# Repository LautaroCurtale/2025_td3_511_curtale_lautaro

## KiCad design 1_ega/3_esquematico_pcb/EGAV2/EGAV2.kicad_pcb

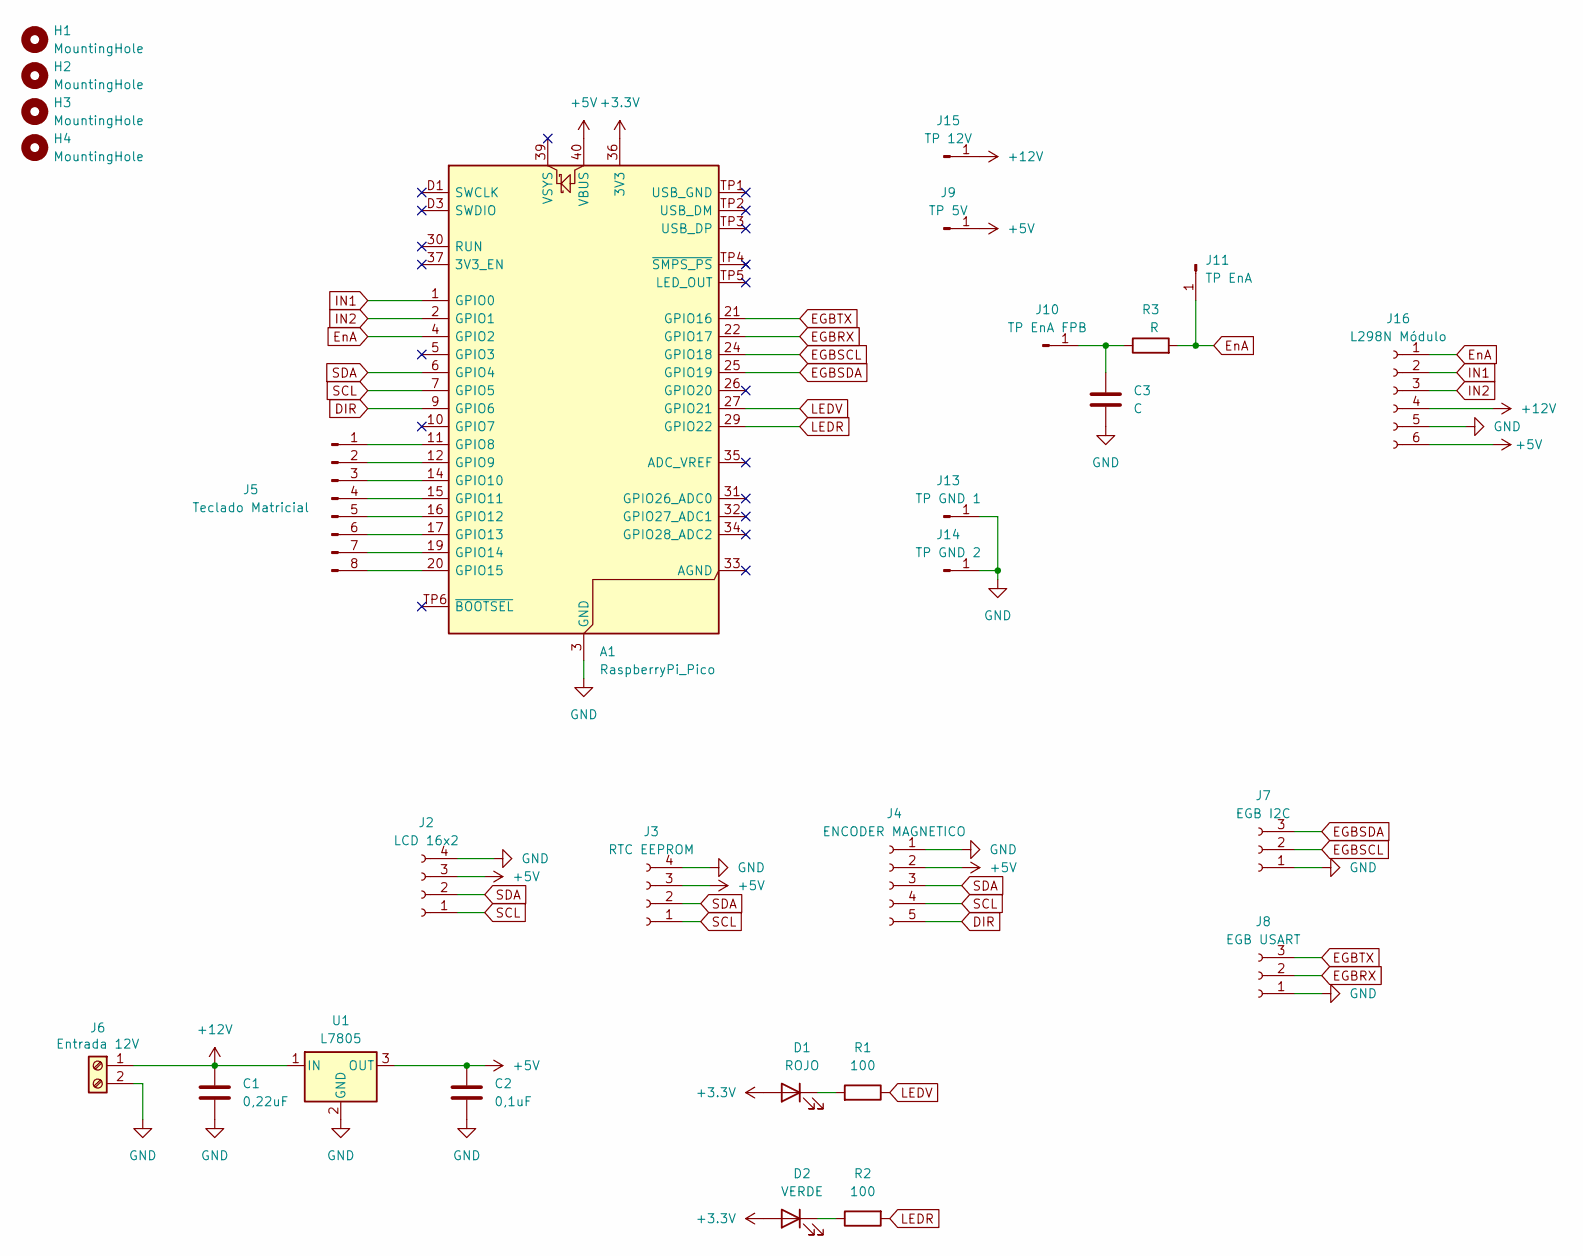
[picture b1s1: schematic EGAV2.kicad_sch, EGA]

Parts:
A1: RaspberryPi_Pico; RaspberryPi_Pico_Common_THT
C1: 0,22uF; C_Disc_D3.0mm_W2.0mm_P2.50mm
C2: 0,1uF; C_Disc_D3.0mm_W2.0mm_P2.50mm
C3: C; C_Disc_D3.0mm_W2.0mm_P2.50mm
D1: ROJO; LED_D5.0mm
D2: VERDE; LED_D5.0mm
H1, H2, H3, H4: MountingHole; MountingHole_3mm
J2: LCD 16x2; PinSocket_1x04_P2.54mm_Vertical
J3: RTC EEPROM; PinSocket_1x04_P2.54mm_Vertical
J4: ENCODER MAGNETICO; PinHeader_1x05_P2.54mm_Vertical
J5: Teclado Matricial; PinHeader_1x08_P2.54mm_Vertical
J6: Entrada 12V; TerminalBlock_Phoenix_MKDS-1,5-2-5.08_1x02_P5.08mm_Horizont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
J7: EGB I2C; PinHeader_1x03_P2.54mm_Vertical
J8: EGB USART; PinHeader_1x03_P2.54mm_Vertical
J9: TP 5V; PinHeader_1x01_P2.54mm_Vertical
J10: TP EnA FPB; PinHeader_1x01_P2.54mm_Vertical
J11: TP EnA; PinHeader_1x01_P2.54mm_Vertical
J13: TP GND 1; PinHeader_1x01_P2.54mm_Vertical
J14: TP GND 2; PinHeader_1x01_P2.54mm_Vertical
J15: TP 12V; PinHeader_1x01_P2.54mm_Vertical
J16: L298N Módulo; PinHeader_1x06_P2.54mm_Vertical
R1, R2: 100; R_Axial_DIN0207_L6.3mm_D2.5mm_P10.16mm_Horizontal
R3: R; R_Axial_DIN0207_L6.3mm_D2.5mm_P10.16mm_Horizontal
U1: L7805; TO-220-3_Vertical

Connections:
+3.3V: A1.36 (3V3), D1.2 (A), D2.2 (A)
+5V: A1.40 (VBUS), C2.2, J2.3, J3.3, J4.2, J9.1, J16.6, U1.3 (OUT)
+12V: C1.1, J6.1, J15.1, J16.4, U1.1 (IN)
DIR: A1.9 (GPIO6), J4.5
EGBRX: A1.22 (GPIO17), J8.2
EGBSCL: A1.24 (GPIO18), J7.2
EGBSDA: A1.25 (GPIO19), J7.3
EGBTX: A1.21 (GPIO16), J8.3
EnA: A1.4 (GPIO2), J11.1, J16.1, R3.2
GND: A1.3 (GND), A1.8 (GND), A1.13 (GND), A1.18 (GND), A1.23 (GND), A1.28 (GND), A1.38 (GND), A1.D2 (GND), C1.2, C2.1, C3.2, J2.4, J3.4, J4.1, J6.2, J7.1, J8.1, J13.1, J14.1, J16.5, U1.2 (GND)
IN1: A1.1 (GPIO0), J16.2
IN2: A1.2 (GPIO1), J16.3
LEDR: A1.29 (GPIO22), R2.2
LEDV: A1.27 (GPIO21), R1.1
unnamed: A1.11 (GPIO8), J5.1
unnamed: A1.12 (GPIO9), J5.2
unnamed: A1.14 (GPIO10), J5.3
unnamed: A1.15 (GPIO11), J5.4
unnamed: A1.16 (GPIO12), J5.5
unnamed: A1.17 (GPIO13), J5.6
unnamed: A1.19 (GPIO14), J5.7
unnamed: A1.20 (GPIO15), J5.8
unnamed: D1.1 (K), R1.2
unnamed: D2.1 (K), R2.1
unnamed: C3.1, J10.1, R3.1
SCL: A1.7 (GPIO5), J2.1, J3.1, J4.4
SDA: A1.6 (GPIO4), J2.2, J3.2, J4.3

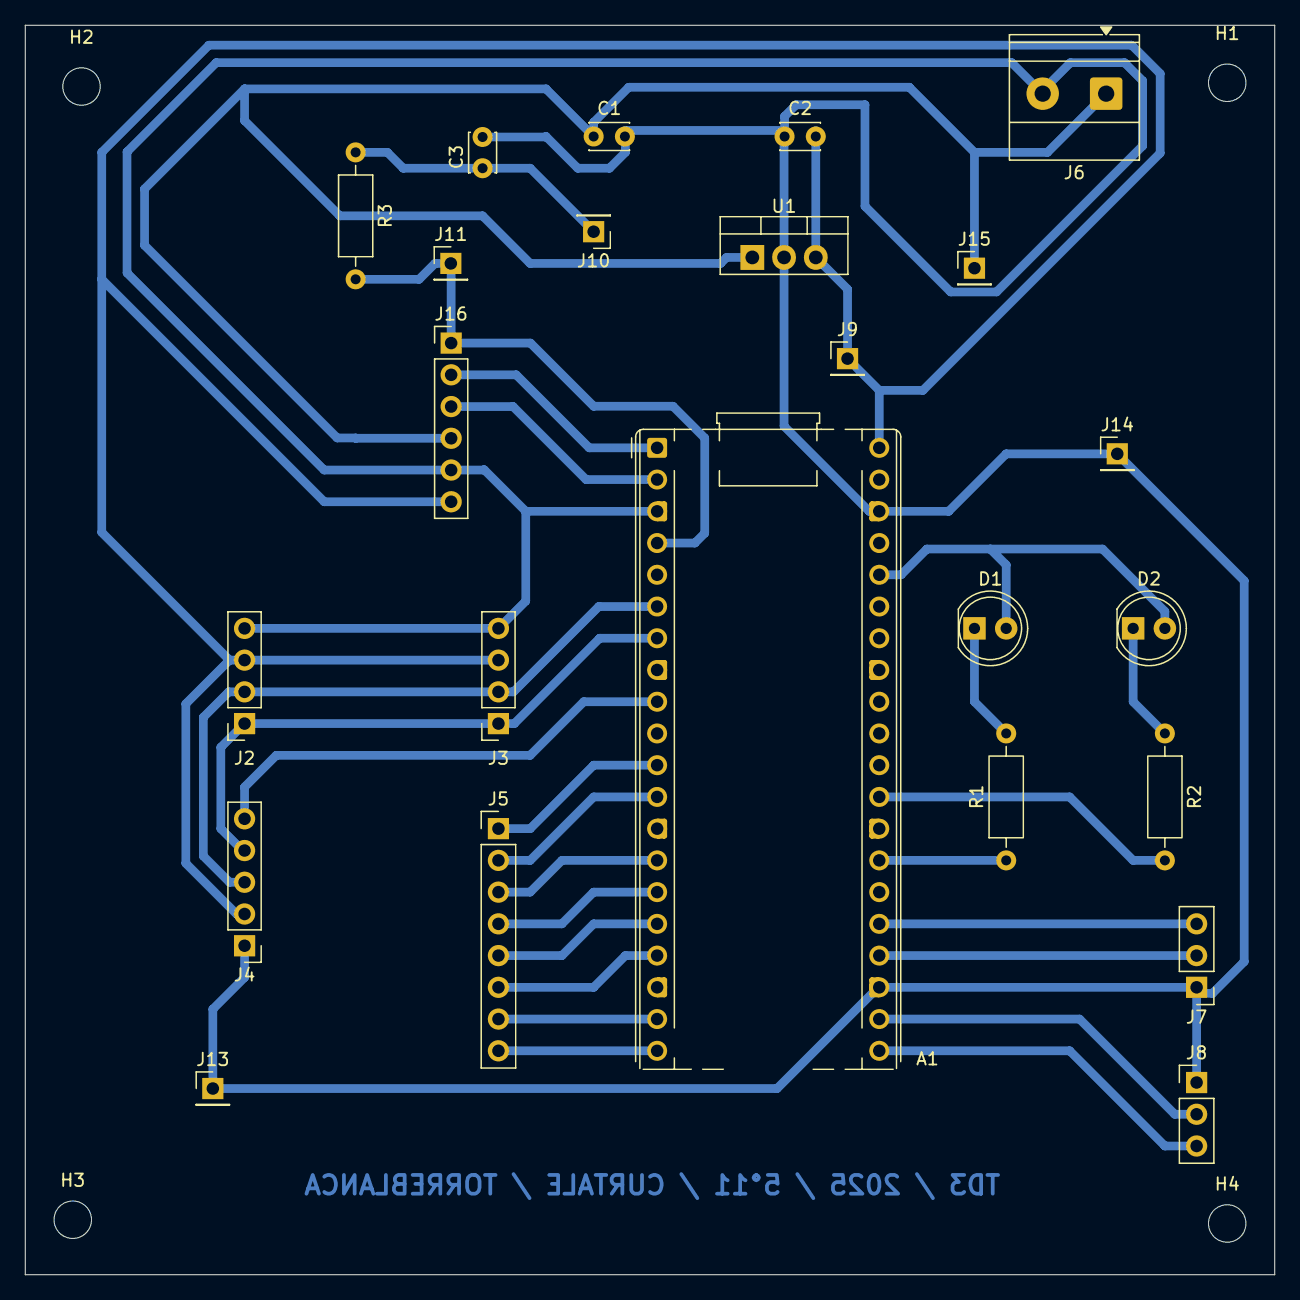
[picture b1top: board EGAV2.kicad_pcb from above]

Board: 2 copper layers, 100.0 x 100.0 mm, 28 parts (0 on the bottom side), 27 nets.

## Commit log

2025-05-29 Primer consigna de TP3
2025-05-29 Segunda consigna de TP3
2025-06-19 Primer consigna de TP4
2025-07-04 Se agrega diagrama en bloques
2025-07-18 Avance codigo
2025-07-18 Esquemático y PCB
2025-07-18 Se agrega diagrama de tareas
2025-07-18 Se agregan librerias
2025-08-05 Agrego librerias
2025-08-05 Cambios en librerias
2025-08-07 Actualizo codigo
2025-08-07 Segunda Consigna TP4
2025-08-07 Guia de Código
2025-08-07 Prueba 1 código
2025-08-09 Anda LCD/Teclado/Lectura
2025-08-09 Checkeo sábado
2025-08-09 Medio funcional Sabado
2025-08-11 Actualizacion Lunes 5 AM
2025-08-13 Probar PID
2025-08-13 Prueba 06:42
2025-08-13 Prueba funcional 09:40
2025-08-13 Programa Final
2025-08-20 Arreglos 13/8
2025-08-24 Version final con pendiente corregida + constantes correctas
2025-08-27 Entrega Final
2025-08-29 Versión final
2025-08-30 Se agregan modelos 3D
2025-09-24 Cambios en los archivos
2025-10-01 Versión corregida
2025-10-16 Primer Consigna de TP5
2025-10-16 Segunda consigna de TP5
2025-11-19 Primeros cambios
2025-11-19 Cambios iniciales
2025-11-26 Pre prueba completa
2025-11-26 Codigo Funcional 100%
2025-12-02 Se agrega activar PWM, error en valor absoluto
2025-12-02 Se agrega activar PWM
2025-12-02 Actualizo página
